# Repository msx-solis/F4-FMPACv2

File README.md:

# F4-FMPACv2
Placa de circuito impreso diseñada a partir del proyecto F4-FMPAC del grupo RSBC.
Este circuito permite mejorar las capacidades musicales de los ordenadores MSX, es compatible con los estándares FMPAC y msxmusic.
La versión 2 está especificamente diseñada para adaptarse a las dimensiones del OMEGA HOME COMPUTER, y a diferencia de la versión anterior su diseño evita tener que soldar componentes de superficie (SMD) para facilitar la construcción por parte de los más novatos.
El circuito dispone de dos tiras de pines en la parte inferior para ser insertadas en el zocalo del procesador z80, que debe ser extraido de la placa base original e instalado en el zócalo destinado a tal efecto en esta placa.
Además requiere de ser alimentado a +12v y -12v porque de lo contrario el OMEGA no iniciará adecuadamente.
La alimentación puede ser suministrada mediante un módulo eletechsup DD1718PA de +12/-12v, instalando este en el zócalo previsto para tal proposito, o bien proporcionando dichos voltages en los pines 3-5 de dicho zócalo.
También requiere la reprogramación de la ROM del sistema para incorporar una extensión del BIOS que dé soporte a este circuito, de lo contrario los programas que soportan la extensión seguirán omitiendo el módulo y utilizando el sistema FM principal.
A diferencia de la versión anterior este PCB no incorpora zócalo para memoria ROM ni señales a tomar de un slot de cartucho.
Como instrucciones de montaje se pueden seguir las publicadas para la versión anterior en:
https://msxmakers.design.blog/proyectos/f4-fmpac/

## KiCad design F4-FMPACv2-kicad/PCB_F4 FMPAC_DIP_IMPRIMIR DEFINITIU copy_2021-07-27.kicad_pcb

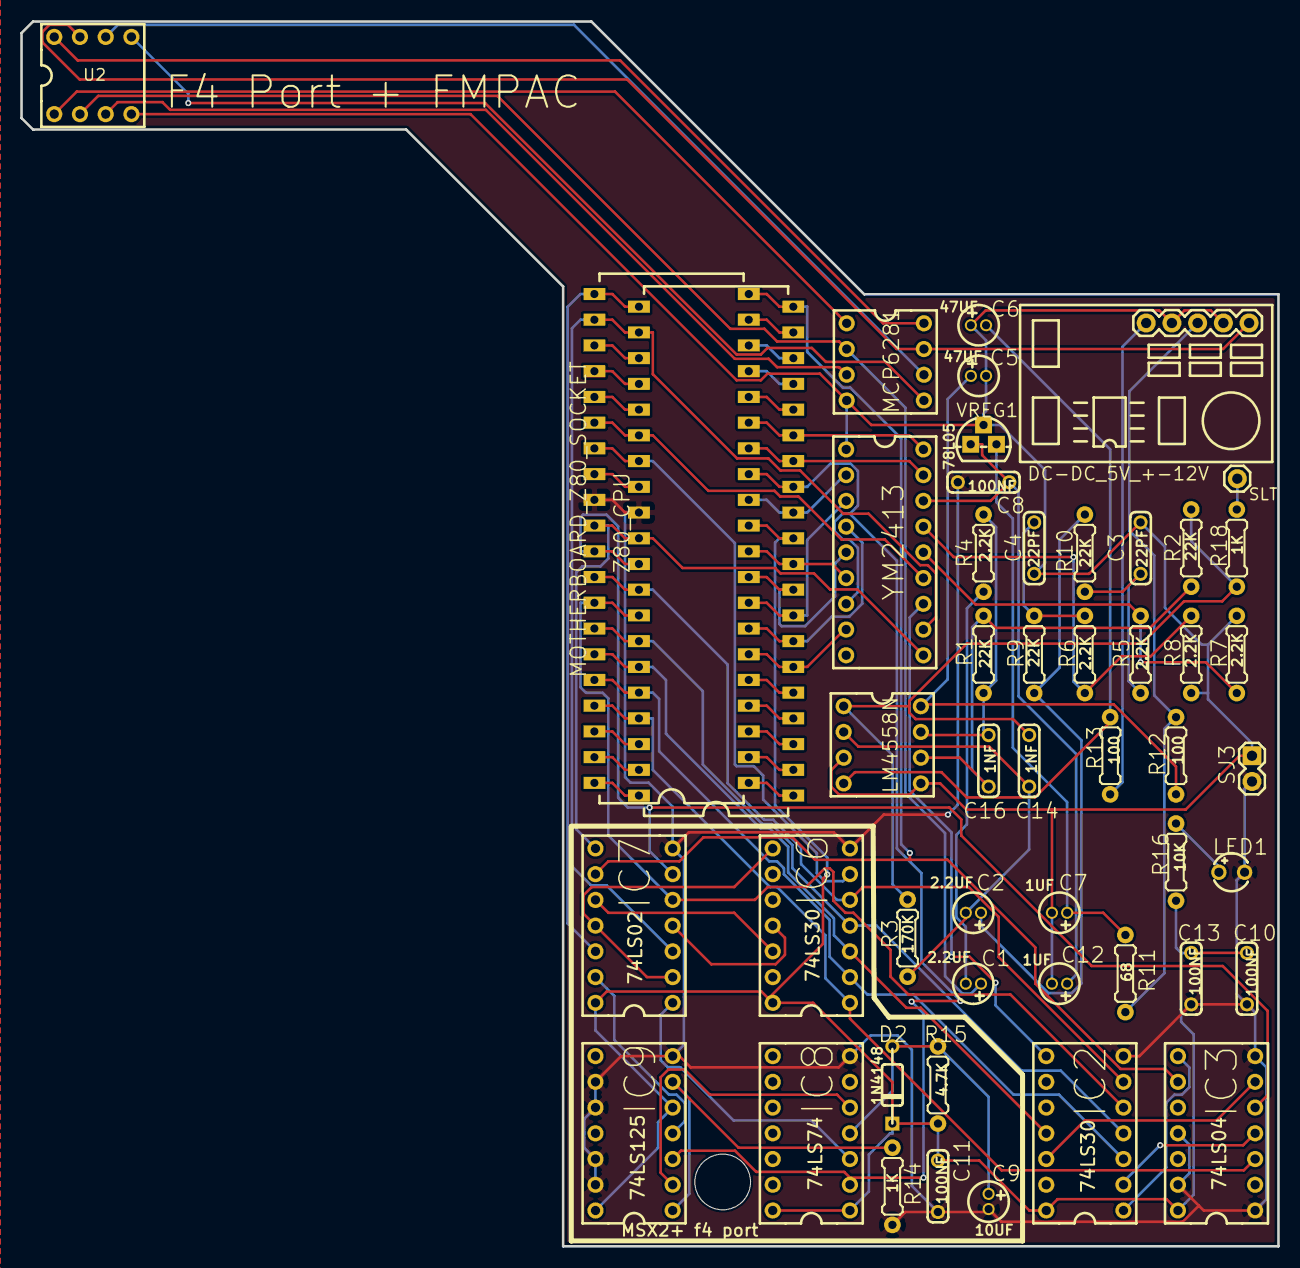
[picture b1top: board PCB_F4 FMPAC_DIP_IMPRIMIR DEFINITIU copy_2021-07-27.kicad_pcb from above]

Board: 2 copper layers, 124.1 x 120.9 mm, 50 parts (0 on the bottom side), 78 nets.

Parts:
C1, C2: 2.2uF25v; CAPACITOR ELECTROLITYC 10UF
C3, C4: 22pF; CAPACITOR OMEGA 0.1UF
C5, C6: 47uF 16v; CAPACITOR ELECTROLITYC 10UF
C7, C12: 1uF 25v; CAPACITOR ELECTROLITYC 10UF
C8, C10, C11, C13: 100nF; CAPACITOR OMEGA 0.1UF
C9: 10uF 16V; CAPACITOR ELECTROLITYC 10UF
C14, C16: 1nF; CAPACITOR OMEGA 0.1UF
D2: 1N4148WSF-7; DIODE_ZENER
DC-DC_5V_+-12V: dc-dc 5v +-12v; DC-DC 5V +-12V
IC2, IC6: 74LS30D; DIP-14
IC3: 74LS04D; DIP-14
IC7: 74LS02D; DIP-14
IC8: 74LS74D; DIP-14
IC9: 74LS125D; DIP-14
LED1: LED 3MM; LED-TH_BD3.8-P2.54-FD
LM4558N: LM4558N; DIP-8
MCP6281: MCP6281; DIP-8
MOTHERBOARD_Z80_SOCKET: DIP40 MB CONN; DIL40
R1, R2, R9, R10: 22k; RESISTOR 1_4W
R3: 170k; RESISTOR 1_4W
R4, R15: 4.7k; RESISTOR 1_4W
R5, R6, R7, R8: 2.2k; RESISTOR 1_4W
R11: 68; RESISTOR 1_4W
R12, R13: 100; RESISTOR 1_4W
R14, R18: 1k; RESISTOR 1_4W
R16: Resistor; RESISTOR 1_4W
SJ3: SJ; 2PIN_CONNECTOR PIN1 0X,0Y
SLT: SLT; 1PIN_CONNECTOR PIN1 0X,0Y
U2: SOCKET DIP; DIP-8
VREG1: 7805L; TO92
YM2413: YM2413; DIP-18
Z80_CPU: Z80; DIL40

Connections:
+5V: C10.1, C11.1, C13.1, D2.1, IC2.14, IC3.14, IC6.14, IC7.14, IC8.1, IC8.14, IC9.5, IC9.14, MOTHERBOARD_Z80_SOCKET.11, R15.1, R16.2, Z80_CPU.11
+5VREG: C8.2, C12.+, VREG1.1, YM2413.16
+12V: DC-DC_5V_+-12V.3, R11.2, R12.2
-12V: DC-DC_5V_+-12V.5, R13.2
A0: IC7.8, MOTHERBOARD_Z80_SOCKET.30, YM2413.10, Z80_CPU.30
A1: IC3.5, IC7.6, MOTHERBOARD_Z80_SOCKET.31, Z80_CPU.31
A2: IC2.6, IC6.5, MOTHERBOARD_Z80_SOCKET.32, Z80_CPU.32
A3: IC2.5, IC7.5, MOTHERBOARD_Z80_SOCKET.33, Z80_CPU.33
A4: IC2.4, IC6.4, MOTHERBOARD_Z80_SOCKET.34, Z80_CPU.34
A5: IC2.11, IC6.3, MOTHERBOARD_Z80_SOCKET.35, Z80_CPU.35
A6: IC2.3, IC6.2, MOTHERBOARD_Z80_SOCKET.36, Z80_CPU.36
A7: IC3.3, IC6.1, MOTHERBOARD_Z80_SOCKET.37, Z80_CPU.37
A8: MOTHERBOARD_Z80_SOCKET.38, Z80_CPU.38
A9: MOTHERBOARD_Z80_SOCKET.39, Z80_CPU.39
A10: MOTHERBOARD_Z80_SOCKET.40, Z80_CPU.40
A11: MOTHERBOARD_Z80_SOCKET.1, Z80_CPU.1
A12: MOTHERBOARD_Z80_SOCKET.2, Z80_CPU.2
A13: MOTHERBOARD_Z80_SOCKET.3, Z80_CPU.3
A14: MOTHERBOARD_Z80_SOCKET.4, Z80_CPU.4
A15: MOTHERBOARD_Z80_SOCKET.5, Z80_CPU.5
AMP: C1.+, MCP6281.2, U2.2
BUSAK: MOTHERBOARD_Z80_SOCKET.23, Z80_CPU.23
BUSRQ: MOTHERBOARD_Z80_SOCKET.25, Z80_CPU.25
C1_-: C1.-, R4.2
C2_+: C2.+, R9.2, R10.2
C2_-: C2.-, C14.1, LM4558N.2, R3.1
C3_2: C3.2, R5.2, R10.1
C4_1: C4.1, R6.2, R9.1
C5_+: C5.+, LM4558N.8, R12.1
C6_-: C6.-, LM4558N.4, R13.1
C7_+: C7.+, R11.1, VREG1.3
CLCK: MOTHERBOARD_Z80_SOCKET.6, YM2413.8, Z80_CPU.6
D0: MOTHERBOARD_Z80_SOCKET.14, YM2413.17, Z80_CPU.14
D1: MOTHERBOARD_Z80_SOCKET.15, YM2413.18, Z80_CPU.15
D2: MOTHERBOARD_Z80_SOCKET.12, YM2413.2, Z80_CPU.12
D3: MOTHERBOARD_Z80_SOCKET.8, YM2413.3, Z80_CPU.8
D4: MOTHERBOARD_Z80_SOCKET.7, YM2413.4, Z80_CPU.7
D5: MOTHERBOARD_Z80_SOCKET.9, YM2413.5, Z80_CPU.9
D6: MOTHERBOARD_Z80_SOCKET.10, YM2413.6, Z80_CPU.10
D7: IC8.2, IC9.3, MOTHERBOARD_Z80_SOCKET.13, YM2413.7, Z80_CPU.13
GND: C8.1, C9.-, C10.2, C11.2, C13.2, IC2.7, IC3.1, IC3.7, IC3.11, IC3.13, IC6.7, IC7.7, IC8.7, IC9.7, IC9.9, IC9.10, IC9.12, IC9.13, LED1.2, MOTHERBOARD_Z80_SOCKET.29, R14.1, SJ3.2, Z80_CPU.29
GND1: C3.1, C4.2, C5.-, C6.+, C7.-, C12.-, DC-DC_5V_+-12V.2, DC-DC_5V_+-12V.4, LM4558N.3, LM4558N.5, MCP6281.4, R7.2, R8.1, SJ3.1, U2.4, VREG1.2, YM2413.1
HALT: MOTHERBOARD_Z80_SOCKET.18, Z80_CPU.18
IC1_12: IC2.8, YM2413.12
IC1_14: R5.1, R7.1, YM2413.14
IC1_15: R6.1, R8.2, YM2413.15
IC2_1: IC2.1, IC3.8
IC2_2: IC2.2, IC3.4
IC2_12: IC2.12, IC3.6
IC4_1: C14.2, LM4558N.1, R2.2, R3.2, R18.1
IC4_6: C16.1, LM4558N.6, R1.1, R2.1
IC4_7: C16.2, LM4558N.7, R1.2, R4.1
IC6_8: IC6.8, IC7.2, IC7.11
IC6_11: IC6.11, IC7.4
IC6_12: IC6.12, IC7.10
IC8_3: IC7.1, IC8.3
IC8_4: C9.+, D2.2, IC8.4, R15.2
IC8_5: IC8.5, IC9.2
IC9_4: IC7.13, IC9.4
INT: MOTHERBOARD_Z80_SOCKET.16, Z80_CPU.16
IORQ: IC3.9, IC7.9, MOTHERBOARD_Z80_SOCKET.20, Z80_CPU.20
LED1_1: LED1.1, R16.1
M1: IC6.6, MOTHERBOARD_Z80_SOCKET.27, Z80_CPU.27
MREQ: MOTHERBOARD_Z80_SOCKET.19, Z80_CPU.19
NMI: MOTHERBOARD_Z80_SOCKET.17, Z80_CPU.17
R14_2: IC9.1, IC9.6, R14.2
RD: IC7.12, MOTHERBOARD_Z80_SOCKET.21, Z80_CPU.21
RFSH: MOTHERBOARD_Z80_SOCKET.28, Z80_CPU.28
RST: MOTHERBOARD_Z80_SOCKET.26, YM2413.13, Z80_CPU.26
SLT: R18.2, SLT.1
U48B_1: MCP6281.1, U2.1
U48B_3: MCP6281.3, U2.3
U48B_5: MCP6281.5, U2.5
U48B_6: MCP6281.6, U2.6
U48B_7: DC-DC_5V_+-12V.1, MCP6281.7, U2.7
U48B_8: MCP6281.8, U2.8
WAIT: MOTHERBOARD_Z80_SOCKET.24, Z80_CPU.24
WR: IC7.3, MOTHERBOARD_Z80_SOCKET.22, YM2413.11, Z80_CPU.22

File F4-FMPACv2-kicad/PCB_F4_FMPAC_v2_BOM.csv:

Reference, Quantity, Value, Footprint, Datasheet
C1 C2 ,2,"2.2uF25v","Capacitor_THT:CP_Radial_D5.0mm_P2.50mm",""
C8 C10 C11 C13 ,4,"100nF","Capacitor_THT:C_Disc_D4.3mm_W1.9mm_P5.00mm",""
C14 C16 ,2,"1nF","Capacitor_THT:C_Disc_D4.3mm_W1.9mm_P5.00mm",""
C3 C4 ,2,"22pF","Capacitor_THT:C_Disc_D4.3mm_W1.9mm_P5.00mm",""
C5 C6 ,2,"47uF 16v","Capacitor_THT:CP_Radial_D7.5mm_P2.50mm",""
C7 C12 ,2,"1uF 25v","Capacitor_THT:CP_Radial_D5.0mm_P2.50mm",""
C9 ,1,"10uF 16V","Capacitor_THT:CP_Radial_D5.0mm_P2.50mm",""
CN1 ,1,"DIP40 MB CONN","Package_DIP:DIP-40_W15.24mm",""
D2 ,1,"1N4148","Diode_THT:D_DO-35_SOD27_P7.62mm_Horizontal","https://assets.nexperia.com/documents/data-sheet/1N4148_1N4448.pdf"
IC1 ,1,"YM2413","Package_DIP:DIP-18_W7.62mm",""
IC2 IC6 ,2,"74LS30D","Package_DIP:DIP-14_W7.62mm",""
IC3 ,1,"74LS04D","Package_DIP:DIP-14_W7.62mm",""
IC4 ,1,"LM4558N","Package_DIP:DIP-8_W7.62mm",""
IC5 ,1,"Z80","Package_DIP:DIP-40_W15.24mm",""
IC7 ,1,"74LS02D","Package_DIP:DIP-14_W7.62mm",""
IC8 ,1,"74LS74D","Package_DIP:DIP-14_W7.62mm",""
IC9 ,1,"74LS125D","Package_DIP:DIP-14_W7.62mm",""
JP1 ,1,"Conn_01x05","Connector_PinHeader_2.54mm:PinHeader_1x05_P2.54mm_Vertical","~"
LED1 ,1,"LED 3mm","LED_THT:LED_D3.0mm","~"
R11 ,1,"68","Resistor_THT:R_Axial_DIN0207_L6.3mm_D2.5mm_P7.62mm_Horizontal",""
R12 R13 ,2,"100","Resistor_THT:R_Axial_DIN0207_L6.3mm_D2.5mm_P7.62mm_Horizontal",""
R14 ,1,"1k","Resistor_THT:R_Axial_DIN0207_L6.3mm_D2.5mm_P7.62mm_Horizontal",""
R15 ,1,"4.7k","Resistor_THT:R_Axial_DIN0207_L6.3mm_D2.5mm_P7.62mm_Horizontal",""
R16 ,1,"470","Resistor_THT:R_Axial_DIN0207_L6.3mm_D2.5mm_P7.62mm_Horizontal",""
R1 R2 R9 R10 ,4,"22k","Resistor_THT:R_Axial_DIN0207_L6.3mm_D2.5mm_P7.62mm_Horizontal",""
R3 ,1,"170k","Resistor_THT:R_Axial_DIN0207_L6.3mm_D2.5mm_P7.62mm_Horizontal",""
R4 R5 R6 R7 R8 ,5,"2.2k","Resistor_THT:R_Axial_DIN0207_L6.3mm_D2.5mm_P7.62mm_Horizontal",""
SJ3 ,1,"SJ","Connector_PinHeader_2.54mm:PinHeader_1x02_P2.54mm_Vertical",""
U2 ,1,"SOCKET DIP","Package_DIP:DIP-8_W7.62mm","http://ww1.microchip.com/downloads/en/DeviceDoc/21314g.pdf"
U48 ,1,"MCP6182","Package_DIP:DIP-8_W7.62mm","http://ww1.microchip.com/downloads/en/DeviceDoc/21314g.pdf"
VREG1 ,1,"78L","Package_TO_SOT_THT:TO-92L_Wide",""

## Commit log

2023-05-12 Create gerber zip
